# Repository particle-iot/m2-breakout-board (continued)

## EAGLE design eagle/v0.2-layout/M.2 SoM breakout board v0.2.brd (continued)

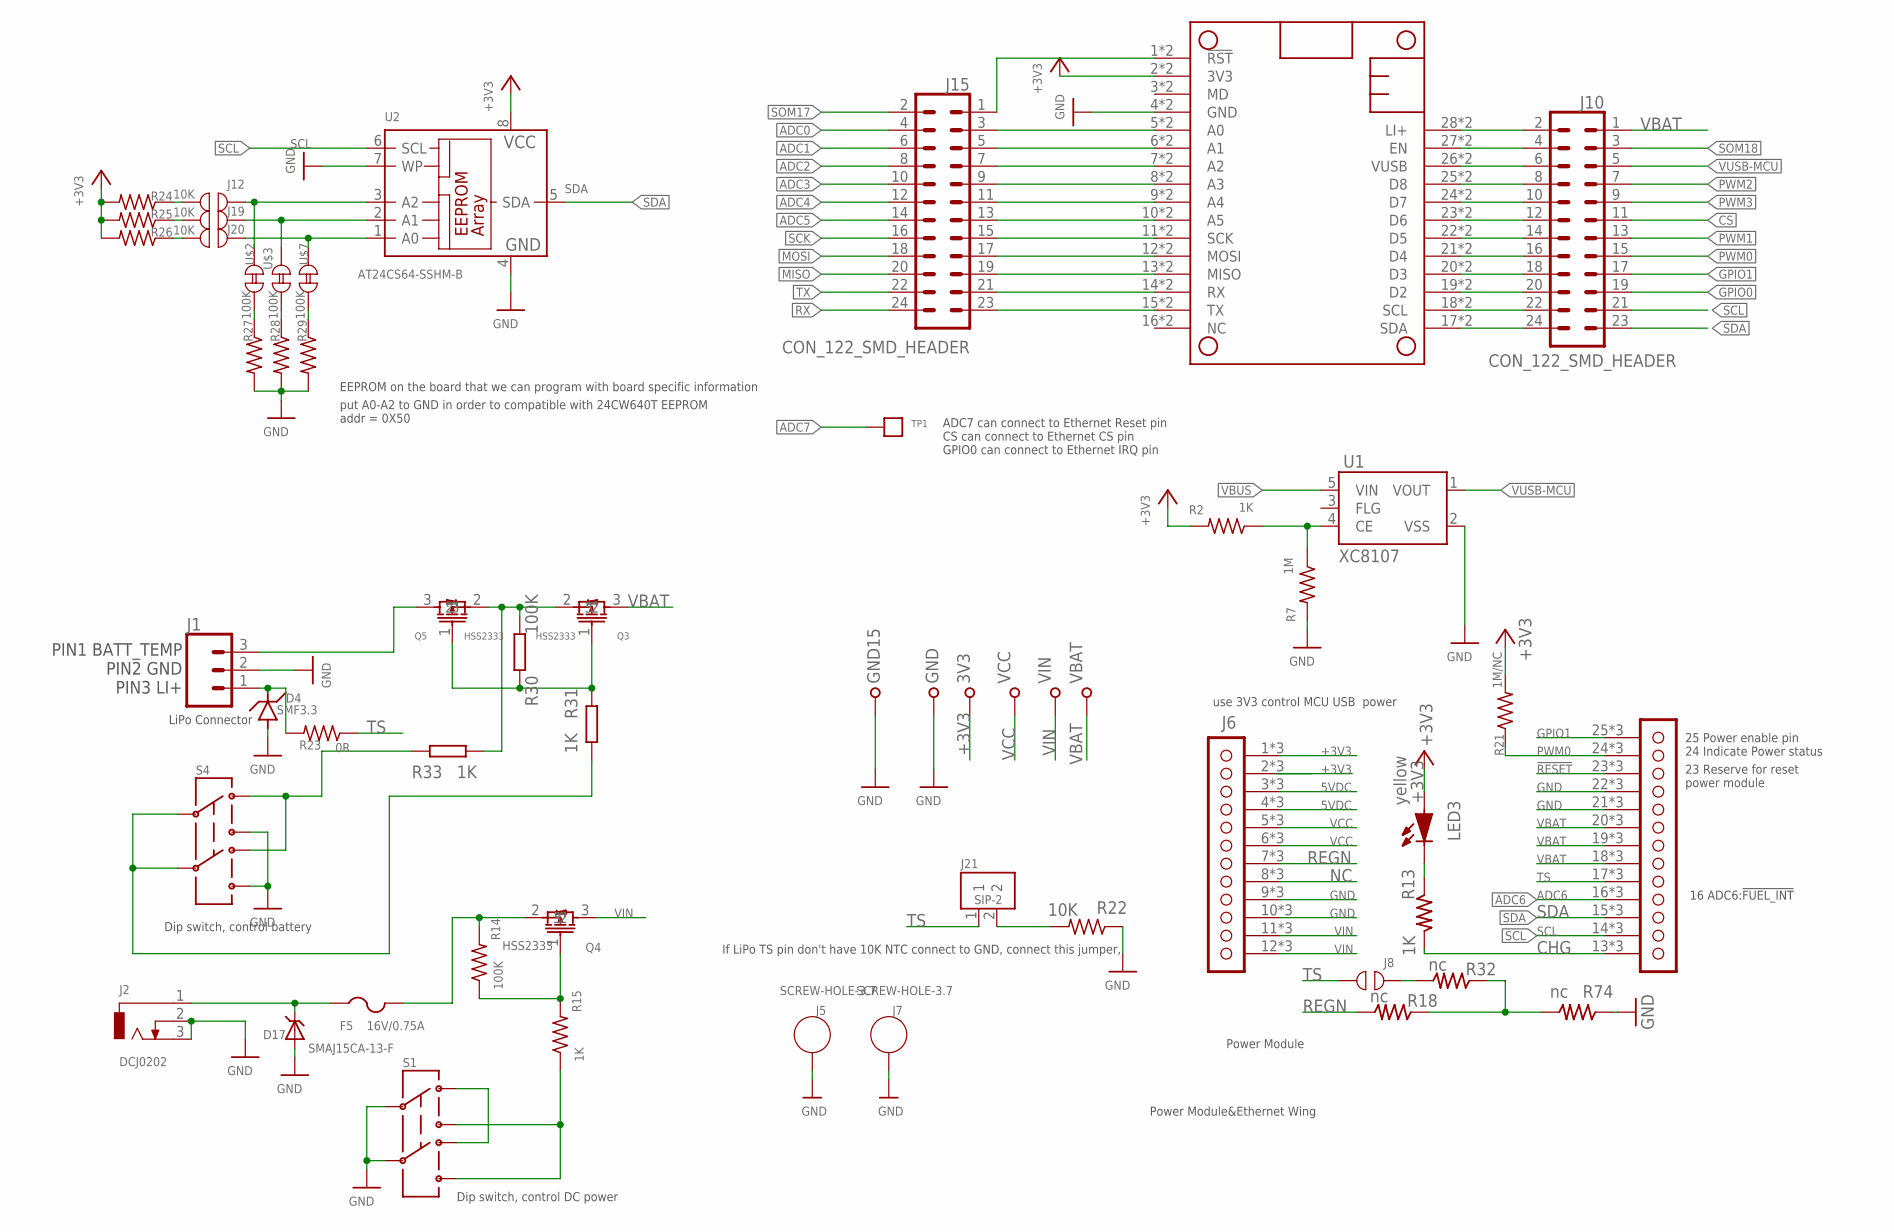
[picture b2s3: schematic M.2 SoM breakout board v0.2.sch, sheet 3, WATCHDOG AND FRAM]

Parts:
3V3: TP-S2751-46R; S2751-46R
D4: SMF3.3; SOD-123FL
D17: SMAJ15CA-13-F; SMADIODE
F5: 16V/0.75A; R1206
GND, GND15: TP-S2751-46R; S2751-46R
J1: CONN_03JST-SMD-VERT; JST-3-SMD-VERT
J2: DCJ0202
J5, J7: SCREW-HOLE-3.7
J6: PARTICLE-SZ_PARTICLE-POWER-MODULE
J8, J12, J19, J20: TP_OPEN
J10, J15: CON_122_SMD_HEADER; CON_12*2_SMD_HEADER
J21: SIP-2
LED3: yellow; LED0603
MS1: PARTICLE_MESH_SMTDUAL; FEATHERWING_SMT2
Q3, Q4, Q5: HSS2333; SOT-23
R2, R15: 1K; R0402_B
R7: 1M; R0402_B
R13, R31, R33: 1K; R-0402S
R14, R27, R28, R29: 100K; R0402_B
R18, R32, R74: nc; R-0402S
R21: 1M/NC; R0402_B
R22: 10K; R0603_P
R23: 0R; R0402_B
R24, R25, R26: 10K; R0402_B
R30: 100K; R0603
S1, S4: SWITCH-DPDT; SWITCH-2.5X3.2-6
TP1: TPTPEB; TPEB
U1: XC8107; SOT25
U2: AT24CS64-SSHM-B; SO-08
U$2, U$3, U$7: TP_SHORT
VBAT: TP-S2751-46R; S2751-46R
VCC: TP-S2751-46R; S2751-46R
VIN: TP-S2751-46R; S2751-46R

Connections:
5VDC: J6.3 (5DC), J6.4 (5DC), J6.@3 (5DC), J6.@4 (5DC), J6.P$3 (5DC), J6.P$4 (5DC)
!RESET: J6.23 (!RST), J6.@23 (!RST), J6.P$23 (!RST); also elsewhere on the board
+3V3: 3V3.1, J6.1 (3V3), J6.2 (3V3), J6.@1 (3V3), J6.@2 (3V3), J6.P$1 (3V3), J6.P$2 (3V3), LED3.1 (A), MS1.2 (3V3), MS1.2' (3V3), R2.2, R21.2, R24.2, R25.2, R26.2, U2.8 (VCC); also elsewhere on the board
ADC0: J15.4; also elsewhere on the board
ADC1: J15.6; also elsewhere on the board
ADC2: J15.8; also elsewhere on the board
ADC3: J15.10; also elsewhere on the board
ADC4: J15.12; also elsewhere on the board
ADC5: J15.14; also elsewhere on the board
ADC6: J6.16 (!FUEL-INT), J6.@16 (!FUEL-INT), J6.P$16 (!FUEL-INT); also elsewhere on the board
ADC7: TP1.1; also elsewhere on the board
CHG: J6.13 (CHG), J6.@13 (CHG), J6.P$13 (CHG), R13.2
CS: J10.11; also elsewhere on the board
GND: D4.A, D17.A, GND.1, GND15.1, J1.2, J2.2, J2.3, J5.P$1, J6.9 (GND), J6.10 (GND), J6.21 (GND), J6.22 (GND), J6.@9 (GND), J6.@10 (GND), J6.@21 (GND), J6.@22 (GND), J6.P$9 (GND), J6.P$10 (GND), J6.P$21 (GND), J6.P$22 (GND), J7.P$1, MS1.4 (GND), MS1.4' (GND), R7.2, R22.1, R27.2, R28.2, R29.2, R74.1, S1.2, S1.5, S4.3, S4.6, U1.2 (VSS), U2.4 (GND), U2.7 (WP); also elsewhere on the board
GPIO0: J10.19; also elsewhere on the board
GPIO1: J6.25 (ENABLE), J6.@25 (ENABLE), J6.P$25 (ENABLE), J10.17; also elsewhere on the board
LI+: J10.2, MS1.28 (LI+), MS1.28' (LI+)
MISO: J15.20; also elsewhere on the board
MOSI: J15.18; also elsewhere on the board
unnamed: D4.C, J1.1, R23.2
unnamed: R2.1, R7.1, U1.4 (CE)
unnamed: F5.2, Q4.2, R14.2
unnamed: LED3.2 (K), R13.1
unnamed: R18.1, R32.1, R74.2
unnamed: J8.2, R32.2
unnamed: J10.10, MS1.24 (D7), MS1.24' (D7)
unnamed: Q4.1, R14.1, R15.2
unnamed: R15.1, S1.3, S1.6
unnamed: R33.1, S4.1, S4.4
unnamed: J15.3, MS1.5 (A0), MS1.5' (A0)
unnamed: J15.5, MS1.6 (A1), MS1.6' (A1)
unnamed: J15.7, MS1.7 (A2), MS1.7' (A2)
unnamed: J15.9, MS1.8 (A3), MS1.8' (A3)
unnamed: J15.11, MS1.9 (A4), MS1.9' (A4)
unnamed: J15.13, MS1.10 (A5), MS1.10' (A5)
unnamed: J15.15, MS1.11 (SCK), MS1.11' (SCK)
unnamed: J15.17, MS1.12 (MOSI), MS1.12' (MOSI)
unnamed: J15.19, MS1.13 (MISO), MS1.13' (MISO)
unnamed: J15.21, MS1.14 (RX), MS1.14' (RX)
unnamed: J15.23, MS1.15 (TX), MS1.15' (TX)
unnamed: S1.1, S1.4
unnamed: J10.24, MS1.17 (SDA), MS1.17' (SDA)
unnamed: J10.22, MS1.18 (SCL), MS1.18' (SCL)
unnamed: J10.20, MS1.19 (D2), MS1.19' (D2)
unnamed: J10.18, MS1.20 (D3), MS1.20' (D3)
unnamed: J10.16, MS1.21 (D4), MS1.21' (D4)
unnamed: J10.14, MS1.22 (D5), MS1.22' (D5)
unnamed: J10.12, MS1.23 (D6), MS1.23' (D6)
unnamed: J10.8, MS1.25 (D8), MS1.25' (D8)
unnamed: J10.4, MS1.27 (EN), MS1.27' (EN)
unnamed: D17.C, F5.1, J2.1
unnamed: J15.1, MS1.1 (!RST), MS1.1' (!RST)
unnamed: R27.1, U$2.1
unnamed: R28.1, U$3.1
unnamed: J12.2, U2.3 (A2), U$2.2
unnamed: J19.2, U2.2 (A1), U$3.2
unnamed: J12.1, R24.1
unnamed: J19.1, R25.1
unnamed: J20.1, R26.1
unnamed: J20.2, U2.1 (A0), U$7.2
unnamed: R29.1, U$7.1
unnamed: J21.2, R22.2
unnamed: J1.3, Q5.3
unnamed: Q3.2, Q5.2, R30.2, R33.2
unnamed: Q3.1, Q5.1, R30.1, R31.1
unnamed: R31.2, S4.2, S4.5
NC: J6.8 (NC), J6.@8 (NC), J6.P$8 (NC)
PWM0: J6.24 (PG), J6.@24 (PG), J6.P$24 (PG), J10.15, R21.1; also elsewhere on the board
PWM1: J10.13; also elsewhere on the board
PWM2: J10.7; also elsewhere on the board
PWM3: J10.9; also elsewhere on the board
REGN: J6.7 (REGN), J6.@7 (REGN), J6.P$7 (REGN), R18.2
RX: J15.24; also elsewhere on the board
SCK: J15.16; also elsewhere on the board
SCL: J6.14 (SCL), J6.@14 (SCL), J6.P$14 (SCL), J10.21, U2.6 (SCL); also elsewhere on the board
SDA: J6.15 (SDA), J6.@15 (SDA), J6.P$15 (SDA), J10.23, U2.5 (SDA); also elsewhere on the board
SOM17: J15.2; also elsewhere on the board
SOM18: J10.3; also elsewhere on the board
TS: J6.17 (TS), J6.@17 (TS), J6.P$17 (TS), J8.1, J21.1, R23.1
TX: J15.22; also elsewhere on the board
V-USB: J10.6, MS1.26 (VUSB), MS1.26' (VUSB)
VBAT: J6.18 (VBAT), J6.19 (VBAT), J6.20 (VBAT), J6.@18 (VBAT), J6.@19 (VBAT), J6.@20 (VBAT), J6.P$18 (VBAT), J6.P$19 (VBAT), J6.P$20 (VBAT), J10.1, Q3.3, VBAT.1
VBUS: U1.5 (VIN); also elsewhere on the board
VCC: J6.5 (VCC), J6.6 (VCC), J6.@5 (VCC), J6.@6 (VCC), J6.P$5 (VCC), J6.P$6 (VCC), VCC.1; also elsewhere on the board
VIN: J6.11 (VIN), J6.12 (VIN), J6.@11 (VIN), J6.@12 (VIN), J6.P$11 (VIN), J6.P$12 (VIN), Q4.3, VIN.1
VUSB-MCU: J10.5, U1.1 (VOUT); also elsewhere on the board

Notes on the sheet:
LiPo Connector
16 ADC6:!FUEL_INT
Power Module
put A0-A2 to GND in order to compatible with 24CW640T EEPROM addr = 0X50
ADC7 can connect to Ethernet Reset pin CS can connect to Ethernet CS pin GPIO0 can connect to Ethernet IRQ pin
EEPROM on the board that we can program with board specific information
Dip switch, control battery
Dip switch, control DC power
use 3V3 control MCU USB power
Power Module&Ethernet Wing
PIN1 BATT_TEMP PIN2 GND PIN3 LI+
If LiPo TS pin don't have 10K NTC connect to GND, connect this jumper,
24 Indicate Power status
25 Power enable pin
23 Reserve for reset power module

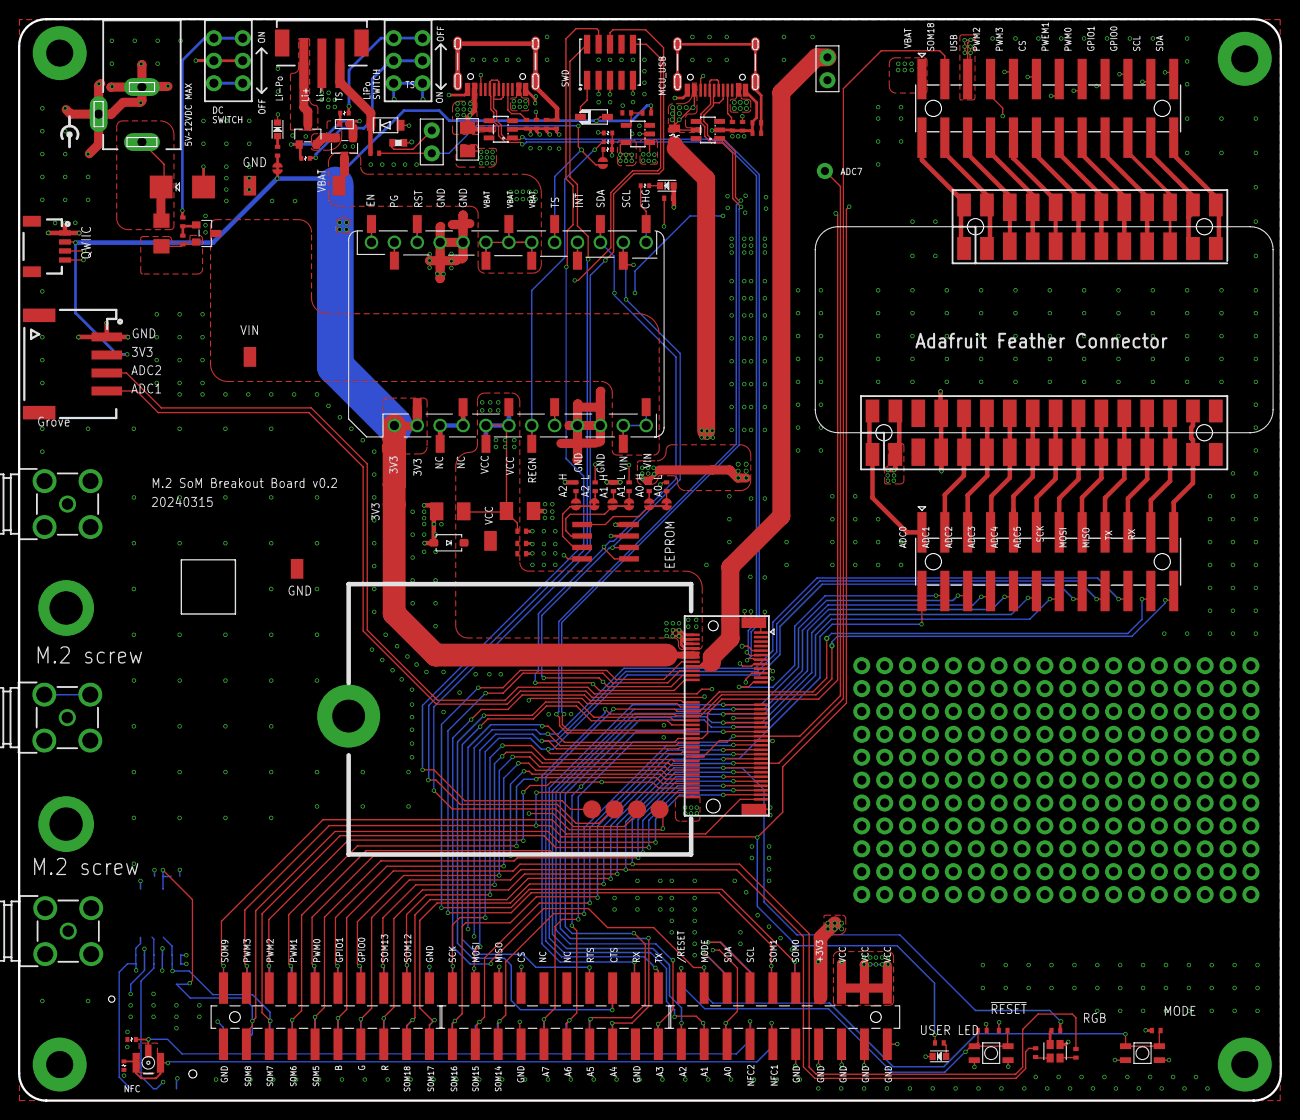
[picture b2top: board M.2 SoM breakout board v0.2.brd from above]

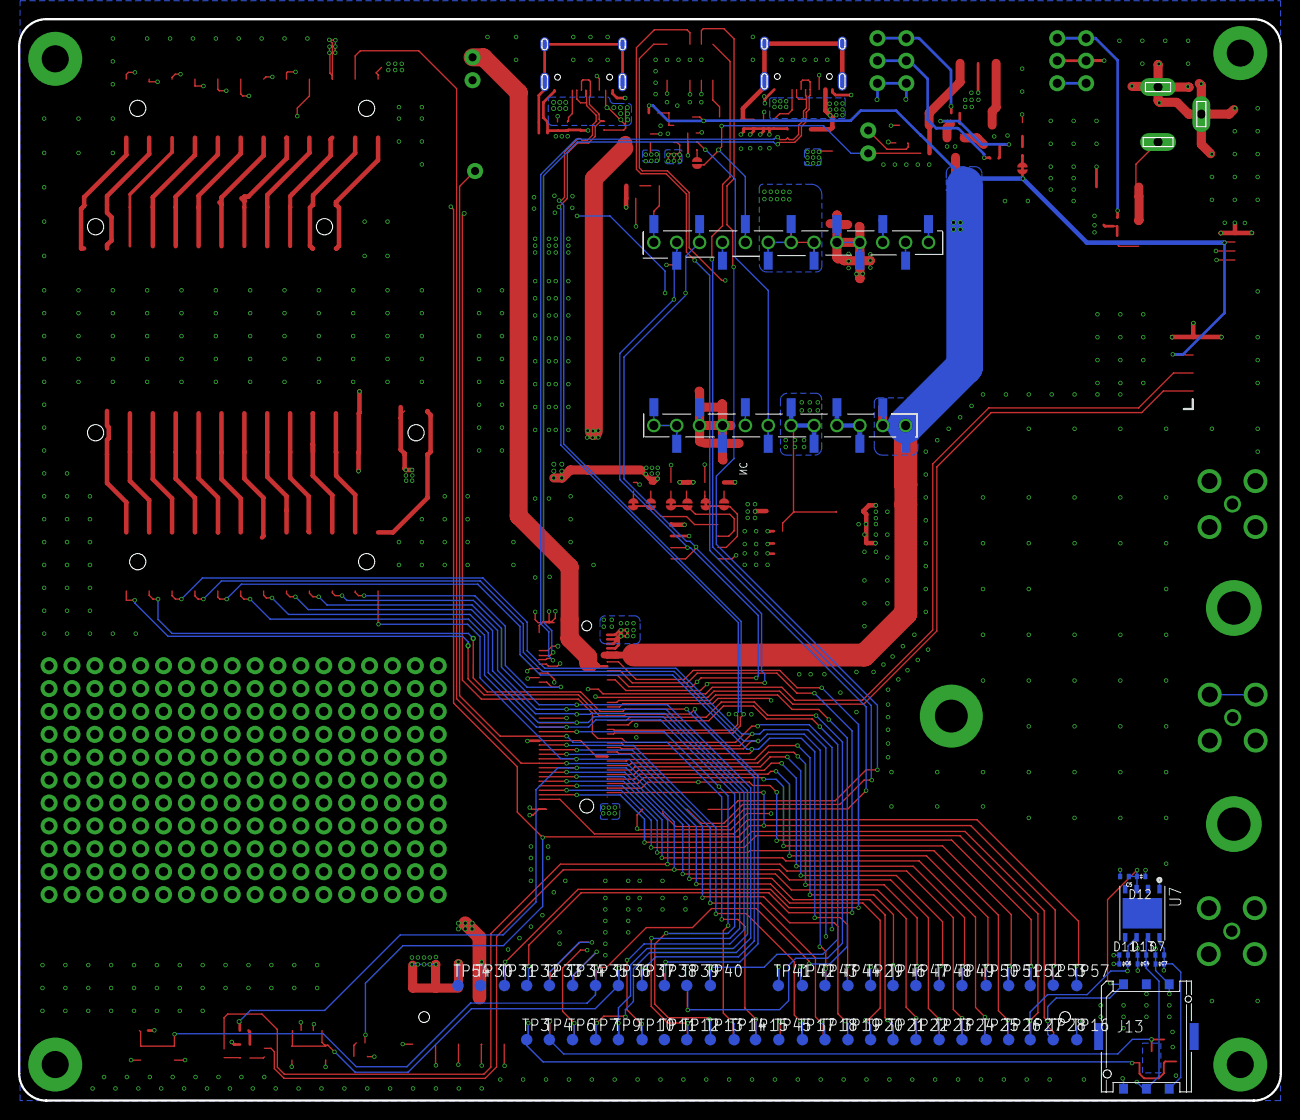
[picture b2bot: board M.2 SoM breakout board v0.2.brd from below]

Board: 4 copper layers, 140.0 x 120.0 mm, 163 parts (61 on the bottom side), 130 nets.

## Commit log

2024-01-12 Create M.2 SoM breakout board
2024-03-05 Update PCB
    Modify the pcb placement
2024-03-11 update placement
    update Power module size of place
2024-03-11 Update M.2 SoM breakout board v0.2-Placement-03011.brd
    update
2024-03-15 update
    complete the layout
2024-03-15 Upadte
    update layout
2024-03-26 update
    1.3.3v power LED 的那个 cutable trace倒是可以去掉
    2.repair CS PIN misstake PIN because of featherwing error silkcreen
    3.Reserve 2 pinholes for jumpers ，GPIO0 is used for IRQ ADC7 is used for RESET
    4.Remove power module EN, PG connections to MSOM and featherwing
2024-03-26 Delete eagle/v0.2 directory
    early pre-placement is no longer needed
2024-03-28 update
    delete based test:
    2 pinholes for jumpers ，GPIO0 is used for IRQ ADC7 is used for RESET that is no needed
2024-04-03 update
    update SCH&PCB
2024-04-04 update
    update PCB&SCH
2024-04-11 updated v0.3 design
    1. Change feather jumpers to smd scratch pads
    2. Align proto area with m.2
    3. Add 3.3V and GND rail along the proto area
    4. LiPo battery pinout change - when we changed from vertical to horizontal, the pinout was flipped. so this is now fixed.
    5. Flipped the TX/RX to match the feather pin out
    6. Removed EN pin connection to feather
2024-04-11 tidy up labels
2024-04-11 update
    update
2024-04-19 update
    1.Repair the silk screen to the jumper,change the size of the circle at the position of the small rubber pad
    2.Remove the jumper from LED1 to 3V3,R16/NC,R17/NC.R11/NC, R22 as 0R ,make the circuit simple that used DC power supply directly control, change the Q1 as nmos and NC reserved
    3.Optimize SPI traces to make them equal in length
2024-04-24 update
    update power module footprint on the breakout
    output gerber for MO DFM
2024-04-29 update
    update based on the feedback
2024-04-30 Added antenna cable clips
    - added antenna cable clips
    - moved qr code square to the bottom left
    - moved VIN test point away from the clip to avoid accidental shorting
    - added GND test point next to VIN test point
2024-05-06 output gerber
    output gerber
2024-05-07 update
    1.Check the DRC again and remove the GND via short circuit bug
    2.Modify the package and test point offset issue
2024-06-03 upload xydate and placement
    upload xydate and placement
2024-08-01 Add v1.0 file.
2024-08-01 Change Q2,Q3,Q4,Q5 value to SI2333DDS
2024-08-02 Create Gerber file
2024-08-02 Modify change log.
2024-08-21 Please refer to change list
    8.Change J6 PCB package,change drill from 1.016mm to 1.3mm. Smaller pad 0.5mm.
    9.Add silkscreen label on the PCB to note that USB is only for comms and not power--"DATA ONLY"
    10.Add 3V3_AUX LED.
    11.Change PCB version to V1.0.
2024-08-21 change R24 value to 1K.
2024-08-26 added pdf of v1.0
2024-08-27 Move Q2 position.
2024-08-27 updated label text and logo on the bottom
2024-08-28 Update V1.0 Gerber file
2024-12-03 typo
2025-08-20 Add CC-BY-SA license
